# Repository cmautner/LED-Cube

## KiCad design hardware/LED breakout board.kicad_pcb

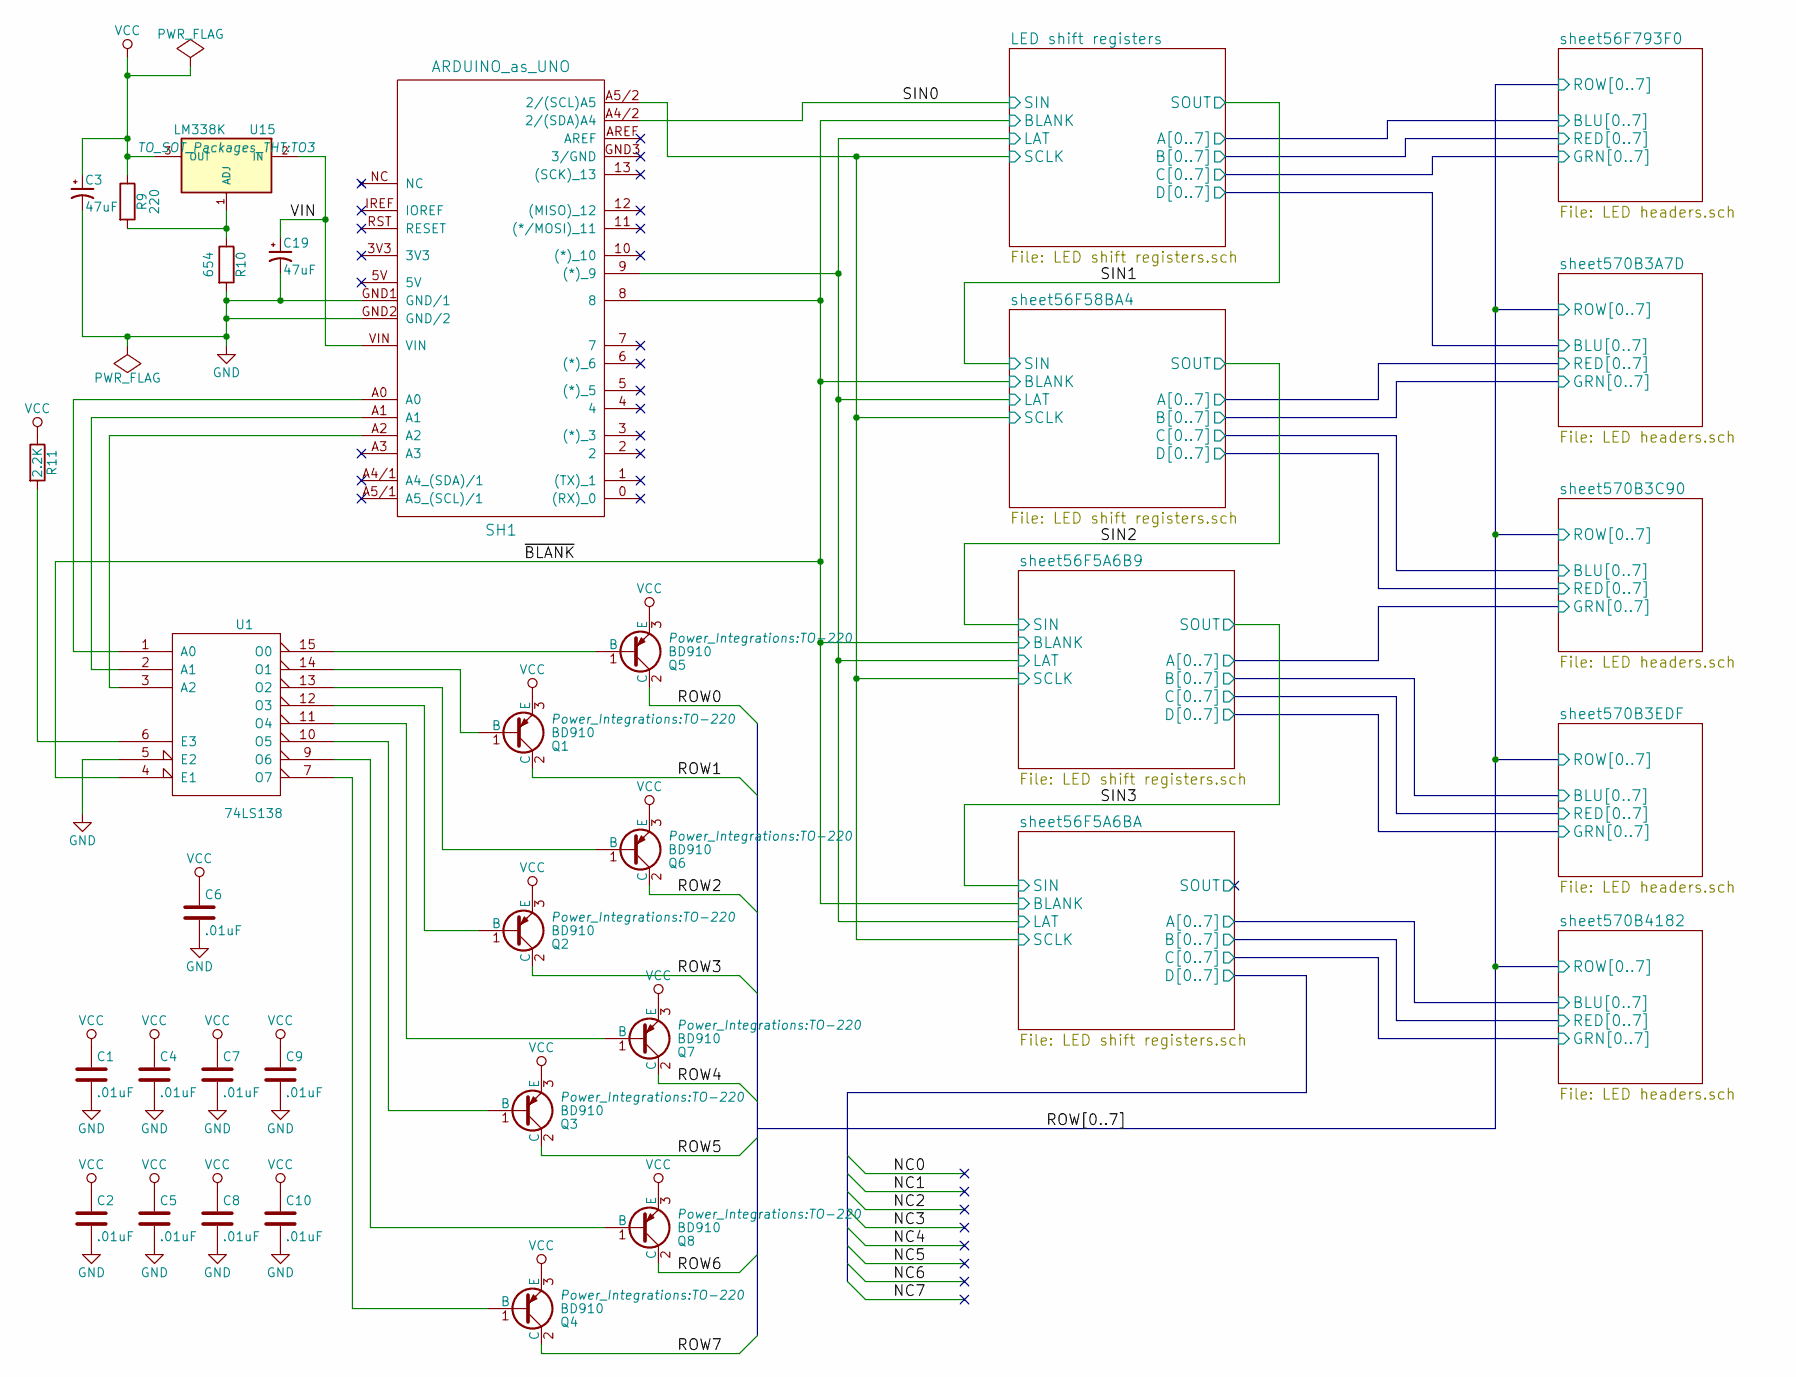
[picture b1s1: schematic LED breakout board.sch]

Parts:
C1, C2, C4, C5, C6, C7, C8, C9, C10: .01uF; C_Disc_D3_P2.5
C3, C19: 47uF; C_Rect_L7_W3.5_P5
Q1, Q2, Q3, Q4, Q5, Q6, Q7, Q8: BD910; TO-220
R9: 220; Resistor_Horizontal_RM10mm
R10: 654; Resistor_Horizontal_RM10mm
R11: 2.2K; Resistor_Horizontal_RM10mm
SH1: ARDUINO_as_UNO; ARDUINO_as_UNO_R3
U1: 74LS138; DIP-16_W7.62mm
U15: LM338K; TO3

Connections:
/LED shift registers/BLANK: SH1.8, U1.4 (E1); also elsewhere on the board
/LED shift registers/LAT: SH1.9 ((*)_9); also elsewhere on the board
/LED shift registers/SCLK: SH1.A5/2 (2/(SCL)A5); also elsewhere on the board
/LED shift registers/SIN: SH1.A4/2 (2/(SDA)A4); also elsewhere on the board
/ROW0: Q5.2 (C); also elsewhere on the board
/ROW1: Q1.2 (C); also elsewhere on the board
/ROW2: Q6.2 (C); also elsewhere on the board
/ROW3: Q2.2 (C); also elsewhere on the board
/ROW4: Q7.2 (C); also elsewhere on the board
/ROW5: Q3.2 (C); also elsewhere on the board
/ROW6: Q8.2 (C); also elsewhere on the board
/ROW7: Q4.2 (C); also elsewhere on the board
/VIN: C19.1, SH1.VIN, U15.2 (IN)
GND: C1.2, C2.2, C3.2, C4.2, C5.2, C6.2, C7.2, C8.2, C9.2, C10.2, C19.2, R10.2, SH1.GND1 (GND/1), SH1.GND2 (GND/2), U1.5 (E2), U1.8 (GND); also elsewhere on the board
unnamed: Q1.1 (B), U1.14 (O1)
unnamed: Q2.1 (B), U1.12 (O3)
unnamed: Q3.1 (B), U1.10 (O5)
unnamed: Q4.1 (B), U1.7 (O7)
unnamed: Q5.1 (B), U1.15 (O0)
unnamed: Q6.1 (B), U1.13 (O2)
unnamed: Q7.1 (B), U1.11 (O4)
unnamed: Q8.1 (B), U1.9 (O6)
unnamed: R9.2, R10.1, U15.1 (ADJ)
unnamed: R11.2, U1.6 (E3)
unnamed: SH1.A0, U1.1 (A0)
unnamed: SH1.A1, U1.2 (A1)
unnamed: SH1.A2, U1.3 (A2)
VCC: C1.1, C2.1, C3.1, C4.1, C5.1, C6.1, C7.1, C8.1, C9.1, C10.1, Q1.3 (E), Q2.3 (E), Q3.3 (E), Q4.3 (E), Q5.3 (E), Q6.3 (E), Q7.3 (E), Q8.3 (E), R9.1, R11.1, U1.16 (VCC), U15.3 (OUT); also elsewhere on the board

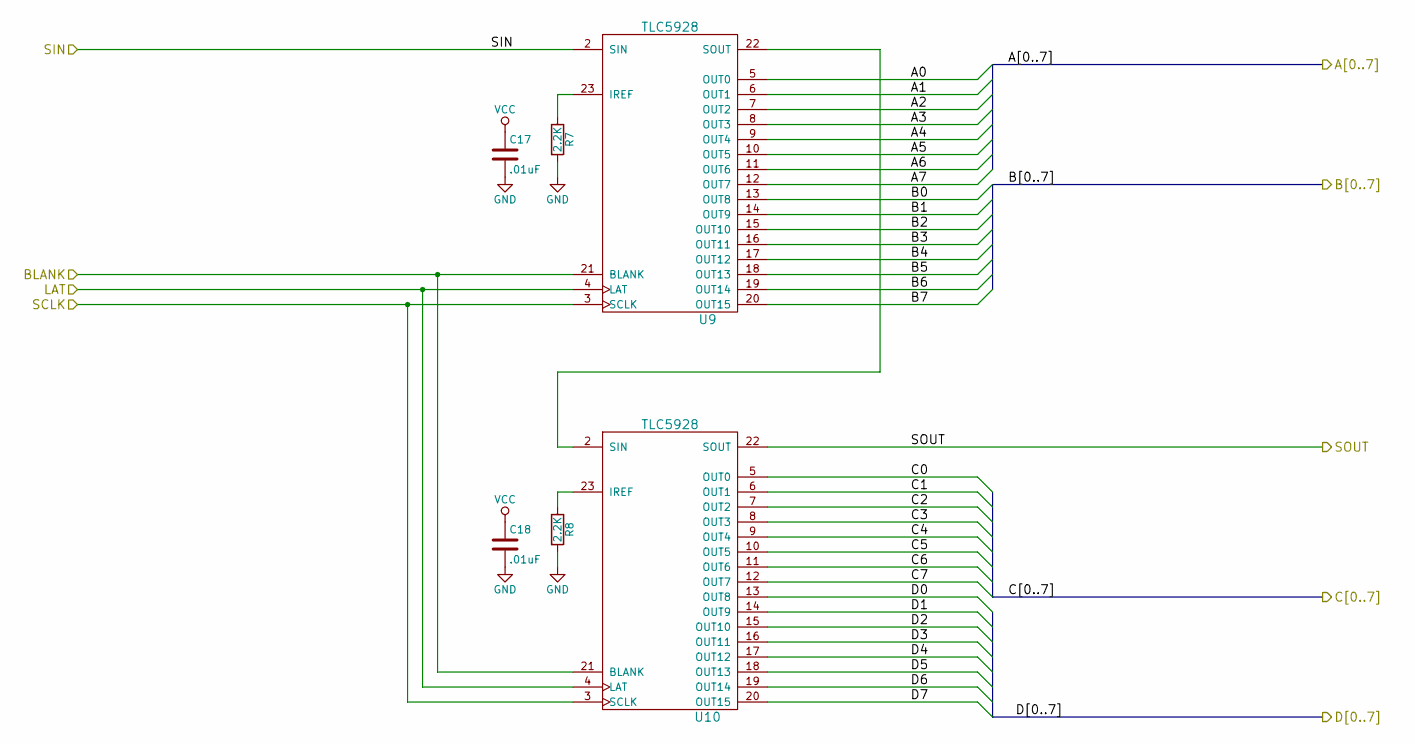
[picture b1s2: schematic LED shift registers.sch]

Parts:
C11, C12: .01uF; C_Disc_D3_P2.5
R1, R2: 2.2K; Resistor_Horizontal_RM10mm
U2, U3: TLC5928; DIP-24_W7.62mm

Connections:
/LED shift registers/A0: U2.5 (OUT0); also elsewhere on the board
/LED shift registers/A1: U2.6 (OUT1); also elsewhere on the board
/LED shift registers/A2: U2.7 (OUT2); also elsewhere on the board
/LED shift registers/A3: U2.8 (OUT3); also elsewhere on the board
/LED shift registers/A4: U2.9 (OUT4); also elsewhere on the board
/LED shift registers/A5: U2.10 (OUT5); also elsewhere on the board
/LED shift registers/A6: U2.11 (OUT6); also elsewhere on the board
/LED shift registers/A7: U2.12 (OUT7); also elsewhere on the board
/LED shift registers/B0: U2.13 (OUT8); also elsewhere on the board
/LED shift registers/B1: U2.14 (OUT9); also elsewhere on the board
/LED shift registers/B2: U2.15 (OUT10); also elsewhere on the board
/LED shift registers/B3: U2.16 (OUT11); also elsewhere on the board
/LED shift registers/B4: U2.17 (OUT12); also elsewhere on the board
/LED shift registers/B5: U2.18 (OUT13); also elsewhere on the board
/LED shift registers/B6: U2.19 (OUT14); also elsewhere on the board
/LED shift registers/B7: U2.20 (OUT15); also elsewhere on the board
/LED shift registers/BLANK: U2.21 (BLANK), U3.21 (BLANK); also elsewhere on the board
/LED shift registers/C0: U3.5 (OUT0); also elsewhere on the board
/LED shift registers/C1: U3.6 (OUT1); also elsewhere on the board
/LED shift registers/C2: U3.7 (OUT2); also elsewhere on the board
/LED shift registers/C3: U3.8 (OUT3); also elsewhere on the board
/LED shift registers/C4: U3.9 (OUT4); also elsewhere on the board
/LED shift registers/C5: U3.10 (OUT5); also elsewhere on the board
/LED shift registers/C6: U3.11 (OUT6); also elsewhere on the board
/LED shift registers/C7: U3.12 (OUT7); also elsewhere on the board
/LED shift registers/LAT: U2.4 (LAT), U3.4 (LAT); also elsewhere on the board
/LED shift registers/SCLK: U2.3 (SCLK), U3.3 (SCLK); also elsewhere on the board
/LED shift registers/SIN: U2.2 (SIN); also elsewhere on the board
/sheet56F58BA4/SIN: U3.22 (SOUT); also elsewhere on the board
/sheet570B3A7D/BLU0: U3.13 (OUT8); also elsewhere on the board
/sheet570B3A7D/BLU1: U3.14 (OUT9); also elsewhere on the board
/sheet570B3A7D/BLU2: U3.15 (OUT10); also elsewhere on the board
/sheet570B3A7D/BLU3: U3.16 (OUT11); also elsewhere on the board
/sheet570B3A7D/BLU4: U3.17 (OUT12); also elsewhere on the board
/sheet570B3A7D/BLU5: U3.18 (OUT13); also elsewhere on the board
/sheet570B3A7D/BLU6: U3.19 (OUT14); also elsewhere on the board
/sheet570B3A7D/BLU7: U3.20 (OUT15); also elsewhere on the board
GND: C11.2, C12.2, R1.2, R2.2, U2.1 (GND), U3.1 (GND); also elsewhere on the board
unnamed: R1.1, U2.23 (IREF)
unnamed: R2.1, U3.23 (IREF)
unnamed: U2.22 (SOUT), U3.2 (SIN)
VCC: C11.1, C12.1, U2.24 (VCC), U3.24 (VCC); also elsewhere on the board

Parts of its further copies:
C13, C14, C15, C16, C17, C18: .01uF; C_Disc_D3_P2.5
R3, R4, R5, R6, R7, R8: 2.2K; Resistor_Horizontal_RM10mm
U4, U5, U6, U7, U9, U10: TLC5928; DIP-24_W7.62mm

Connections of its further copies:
/LED shift registers/BLANK: U4.21 (BLANK), U5.21 (BLANK), U6.21 (BLANK), U7.21 (BLANK), U9.21 (BLANK), U10.21 (BLANK); also elsewhere on the board
/LED shift registers/LAT: U4.4 (LAT), U5.4 (LAT), U6.4 (LAT), U7.4 (LAT), U9.4 (LAT), U10.4 (LAT); also elsewhere on the board
/LED shift registers/SCLK: U4.3 (SCLK), U5.3 (SCLK), U6.3 (SCLK), U7.3 (SCLK), U9.3 (SCLK), U10.3 (SCLK); also elsewhere on the board
/sheet56F5A6B9/A0: U4.5 (OUT0); also elsewhere on the board
/sheet56F5A6B9/A1: U4.6 (OUT1); also elsewhere on the board
/sheet56F5A6B9/A2: U4.7 (OUT2); also elsewhere on the board
/sheet56F5A6B9/A3: U4.8 (OUT3); also elsewhere on the board
/sheet56F5A6B9/A4: U4.9 (OUT4); also elsewhere on the board
/sheet56F5A6B9/A5: U4.10 (OUT5); also elsewhere on the board
/sheet56F5A6B9/A6: U4.11 (OUT6); also elsewhere on the board
/sheet56F5A6B9/A7: U4.12 (OUT7); also elsewhere on the board
/sheet56F5A6B9/B0: U4.13 (OUT8); also elsewhere on the board
/sheet56F5A6B9/B1: U4.14 (OUT9); also elsewhere on the board
/sheet56F5A6B9/B2: U4.15 (OUT10); also elsewhere on the board
/sheet56F5A6B9/B3: U4.16 (OUT11); also elsewhere on the board
/sheet56F5A6B9/B4: U4.17 (OUT12); also elsewhere on the board
/sheet56F5A6B9/B5: U4.18 (OUT13); also elsewhere on the board
/sheet56F5A6B9/B6: U4.19 (OUT14); also elsewhere on the board
/sheet56F5A6B9/B7: U4.20 (OUT15); also elsewhere on the board
/sheet56F5A6B9/C0: U5.5 (OUT0); also elsewhere on the board
/sheet56F5A6B9/C1: U5.6 (OUT1); also elsewhere on the board
/sheet56F5A6B9/C2: U5.7 (OUT2); also elsewhere on the board
/sheet56F5A6B9/C3: U5.8 (OUT3); also elsewhere on the board
/sheet56F5A6B9/C4: U5.9 (OUT4); also elsewhere on the board
/sheet56F5A6B9/C5: U5.10 (OUT5); also elsewhere on the board
/sheet56F5A6B9/C6: U5.11 (OUT6); also elsewhere on the board
/sheet56F5A6B9/C7: U5.12 (OUT7); also elsewhere on the board
/sheet56F5A6B9/D0: U5.13 (OUT8); also elsewhere on the board
/sheet56F5A6B9/D1: U5.14 (OUT9); also elsewhere on the board
/sheet56F5A6B9/D2: U5.15 (OUT10); also elsewhere on the board
/sheet56F5A6B9/D3: U5.16 (OUT11); also elsewhere on the board
/sheet56F5A6B9/D4: U5.17 (OUT12); also elsewhere on the board
/sheet56F5A6B9/D5: U5.18 (OUT13); also elsewhere on the board
/sheet56F5A6B9/D6: U5.19 (OUT14); also elsewhere on the board
/sheet56F5A6B9/D7: U5.20 (OUT15); also elsewhere on the board
/sheet56F5A6B9/SIN: U4.2 (SIN), U10.22 (SOUT)
/sheet56F5A6BA/A0: U6.5 (OUT0); also elsewhere on the board
/sheet56F5A6BA/A1: U6.6 (OUT1); also elsewhere on the board
/sheet56F5A6BA/A2: U6.7 (OUT2); also elsewhere on the board
/sheet56F5A6BA/A3: U6.8 (OUT3); also elsewhere on the board
/sheet56F5A6BA/A4: U6.9 (OUT4); also elsewhere on the board
/sheet56F5A6BA/A5: U6.10 (OUT5); also elsewhere on the board
/sheet56F5A6BA/A6: U6.11 (OUT6); also elsewhere on the board
/sheet56F5A6BA/A7: U6.12 (OUT7); also elsewhere on the board
/sheet56F5A6BA/B0: U6.13 (OUT8); also elsewhere on the board
/sheet56F5A6BA/B1: U6.14 (OUT9); also elsewhere on the board
/sheet56F5A6BA/B2: U6.15 (OUT10); also elsewhere on the board
/sheet56F5A6BA/B3: U6.16 (OUT11); also elsewhere on the board
/sheet56F5A6BA/B4: U6.17 (OUT12); also elsewhere on the board
/sheet56F5A6BA/B5: U6.18 (OUT13); also elsewhere on the board
/sheet56F5A6BA/B6: U6.19 (OUT14); also elsewhere on the board
/sheet56F5A6BA/B7: U6.20 (OUT15); also elsewhere on the board
/sheet56F5A6BA/C0: U7.5 (OUT0); also elsewhere on the board
/sheet56F5A6BA/C1: U7.6 (OUT1); also elsewhere on the board
/sheet56F5A6BA/C2: U7.7 (OUT2); also elsewhere on the board
/sheet56F5A6BA/C3: U7.8 (OUT3); also elsewhere on the board
/sheet56F5A6BA/C4: U7.9 (OUT4); also elsewhere on the board
/sheet56F5A6BA/C5: U7.10 (OUT5); also elsewhere on the board
/sheet56F5A6BA/C6: U7.11 (OUT6); also elsewhere on the board
/sheet56F5A6BA/C7: U7.12 (OUT7); also elsewhere on the board
/sheet56F5A6BA/SIN: U5.22 (SOUT), U6.2 (SIN)
/sheet56F58BA4/A0: U9.5 (OUT0); also elsewhere on the board
/sheet56F58BA4/A1: U9.6 (OUT1); also elsewhere on the board
/sheet56F58BA4/A2: U9.7 (OUT2); also elsewhere on the board
/sheet56F58BA4/A3: U9.8 (OUT3); also elsewhere on the board
/sheet56F58BA4/A4: U9.9 (OUT4); also elsewhere on the board
/sheet56F58BA4/A5: U9.10 (OUT5); also elsewhere on the board
/sheet56F58BA4/A6: U9.11 (OUT6); also elsewhere on the board
/sheet56F58BA4/A7: U9.12 (OUT7); also elsewhere on the board
/sheet56F58BA4/B0: U9.13 (OUT8); also elsewhere on the board
/sheet56F58BA4/B1: U9.14 (OUT9); also elsewhere on the board
/sheet56F58BA4/B2: U9.15 (OUT10); also elsewhere on the board
/sheet56F58BA4/B3: U9.16 (OUT11); also elsewhere on the board
/sheet56F58BA4/B4: U9.17 (OUT12); also elsewhere on the board
/sheet56F58BA4/B5: U9.18 (OUT13); also elsewhere on the board
/sheet56F58BA4/B6: U9.19 (OUT14); also elsewhere on the board
/sheet56F58BA4/B7: U9.20 (OUT15); also elsewhere on the board
/sheet56F58BA4/D0: U10.13 (OUT8); also elsewhere on the board
/sheet56F58BA4/D1: U10.14 (OUT9); also elsewhere on the board
/sheet56F58BA4/D2: U10.15 (OUT10); also elsewhere on the board
/sheet56F58BA4/D3: U10.16 (OUT11); also elsewhere on the board
/sheet56F58BA4/D4: U10.17 (OUT12); also elsewhere on the board
/sheet56F58BA4/D5: U10.18 (OUT13); also elsewhere on the board
/sheet56F58BA4/D6: U10.19 (OUT14); also elsewhere on the board
/sheet56F58BA4/D7: U10.20 (OUT15); also elsewhere on the board
/sheet56F58BA4/SIN: U9.2 (SIN); also elsewhere on the board
/sheet570B3C90/BLU0: U10.5 (OUT0); also elsewhere on the board
/sheet570B3C90/BLU1: U10.6 (OUT1); also elsewhere on the board
/sheet570B3C90/BLU2: U10.7 (OUT2); also elsewhere on the board
/sheet570B3C90/BLU3: U10.8 (OUT3); also elsewhere on the board
/sheet570B3C90/BLU4: U10.9 (OUT4); also elsewhere on the board
/sheet570B3C90/BLU5: U10.10 (OUT5); also elsewhere on the board
/sheet570B3C90/BLU6: U10.11 (OUT6); also elsewhere on the board
/sheet570B3C90/BLU7: U10.12 (OUT7); also elsewhere on the board
GND: C13.2, C14.2, C15.2, C16.2, C17.2, C18.2, R3.2, R4.2, R5.2, R6.2, R7.2, R8.2, U4.1 (GND), U5.1 (GND), U6.1 (GND), U7.1 (GND), U9.1 (GND), U10.1 (GND); also elsewhere on the board
unnamed: R3.1, U4.23 (IREF)
unnamed: R4.1, U5.23 (IREF)
unnamed: R5.1, U6.23 (IREF)
unnamed: R6.1, U7.23 (IREF)
unnamed: R7.1, U9.23 (IREF)
unnamed: R8.1, U10.23 (IREF)
unnamed: U4.22 (SOUT), U5.2 (SIN)
unnamed: U6.22 (SOUT), U7.2 (SIN)
unnamed: U9.22 (SOUT), U10.2 (SIN)
VCC: C13.1, C14.1, C15.1, C16.1, C17.1, C18.1, U4.24 (VCC), U5.24 (VCC), U6.24 (VCC), U7.24 (VCC), U9.24 (VCC), U10.24 (VCC); also elsewhere on the board

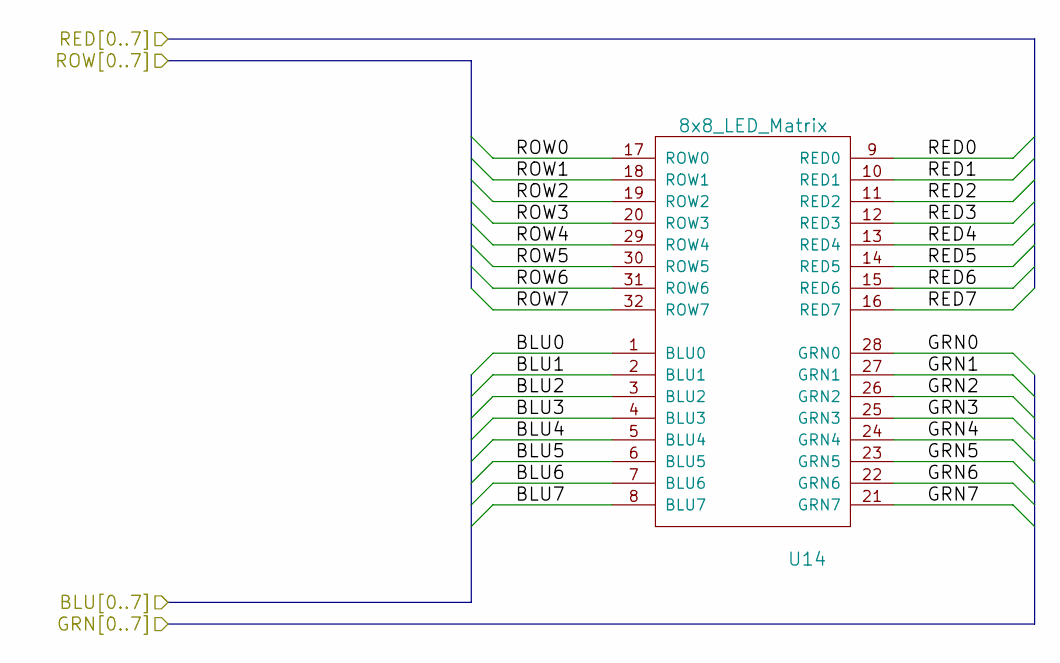
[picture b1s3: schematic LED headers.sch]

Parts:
U8: 8x8_LED_Matrix

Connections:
/LED shift registers/A0: U8.1 (BLU0); also elsewhere on the board
/LED shift registers/A1: U8.2 (BLU1); also elsewhere on the board
/LED shift registers/A2: U8.3 (BLU2); also elsewhere on the board
/LED shift registers/A3: U8.4 (BLU3); also elsewhere on the board
/LED shift registers/A4: U8.5 (BLU4); also elsewhere on the board
/LED shift registers/A5: U8.6 (BLU5); also elsewhere on the board
/LED shift registers/A6: U8.7 (BLU6); also elsewhere on the board
/LED shift registers/A7: U8.8 (BLU7); also elsewhere on the board
/LED shift registers/B0: U8.9 (RED0); also elsewhere on the board
/LED shift registers/B1: U8.10 (RED1); also elsewhere on the board
/LED shift registers/B2: U8.11 (RED2); also elsewhere on the board
/LED shift registers/B3: U8.12 (RED3); also elsewhere on the board
/LED shift registers/B4: U8.13 (RED4); also elsewhere on the board
/LED shift registers/B5: U8.14 (RED5); also elsewhere on the board
/LED shift registers/B6: U8.15 (RED6); also elsewhere on the board
/LED shift registers/B7: U8.16 (RED7); also elsewhere on the board
/LED shift registers/C0: U8.28 (GRN0); also elsewhere on the board
/LED shift registers/C1: U8.27 (GRN1); also elsewhere on the board
/LED shift registers/C2: U8.26 (GRN2); also elsewhere on the board
/LED shift registers/C3: U8.25 (GRN3); also elsewhere on the board
/LED shift registers/C4: U8.24 (GRN4); also elsewhere on the board
/LED shift registers/C5: U8.23 (GRN5); also elsewhere on the board
/LED shift registers/C6: U8.22 (GRN6); also elsewhere on the board
/LED shift registers/C7: U8.21 (GRN7); also elsewhere on the board
/ROW0: U8.17 (ROW0); also elsewhere on the board
/ROW1: U8.18 (ROW1); also elsewhere on the board
/ROW2: U8.19 (ROW2); also elsewhere on the board
/ROW3: U8.20 (ROW3); also elsewhere on the board
/ROW4: U8.29 (ROW4); also elsewhere on the board
/ROW5: U8.30 (ROW5); also elsewhere on the board
/ROW6: U8.31 (ROW6); also elsewhere on the board
/ROW7: U8.32 (ROW7); also elsewhere on the board

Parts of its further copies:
U11, U12, U13, U14: 8x8_LED_Matrix

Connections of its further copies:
/ROW0: U11.17 (ROW0), U12.17 (ROW0), U13.17 (ROW0), U14.17 (ROW0); also elsewhere on the board
/ROW1: U11.18 (ROW1), U12.18 (ROW1), U13.18 (ROW1), U14.18 (ROW1); also elsewhere on the board
/ROW2: U11.19 (ROW2), U12.19 (ROW2), U13.19 (ROW2), U14.19 (ROW2); also elsewhere on the board
/ROW3: U11.20 (ROW3), U12.20 (ROW3), U13.20 (ROW3), U14.20 (ROW3); also elsewhere on the board
/ROW4: U11.29 (ROW4), U12.29 (ROW4), U13.29 (ROW4), U14.29 (ROW4); also elsewhere on the board
/ROW5: U11.30 (ROW5), U12.30 (ROW5), U13.30 (ROW5), U14.30 (ROW5); also elsewhere on the board
/ROW6: U11.31 (ROW6), U12.31 (ROW6), U13.31 (ROW6), U14.31 (ROW6); also elsewhere on the board
/ROW7: U11.32 (ROW7), U12.32 (ROW7), U13.32 (ROW7), U14.32 (ROW7); also elsewhere on the board
/sheet56F5A6B9/A0: U12.28 (GRN0); also elsewhere on the board
/sheet56F5A6B9/A1: U12.27 (GRN1); also elsewhere on the board
/sheet56F5A6B9/A2: U12.26 (GRN2); also elsewhere on the board
/sheet56F5A6B9/A3: U12.25 (GRN3); also elsewhere on the board
/sheet56F5A6B9/A4: U12.24 (GRN4); also elsewhere on the board
/sheet56F5A6B9/A5: U12.23 (GRN5); also elsewhere on the board
/sheet56F5A6B9/A6: U12.22 (GRN6); also elsewhere on the board
/sheet56F5A6B9/A7: U12.21 (GRN7); also elsewhere on the board
/sheet56F5A6B9/B0: U13.1 (BLU0); also elsewhere on the board
/sheet56F5A6B9/B1: U13.2 (BLU1); also elsewhere on the board
/sheet56F5A6B9/B2: U13.3 (BLU2); also elsewhere on the board
/sheet56F5A6B9/B3: U13.4 (BLU3); also elsewhere on the board
/sheet56F5A6B9/B4: U13.5 (BLU4); also elsewhere on the board
/sheet56F5A6B9/B5: U13.6 (BLU5); also elsewhere on the board
/sheet56F5A6B9/B6: U13.7 (BLU6); also elsewhere on the board
/sheet56F5A6B9/B7: U13.8 (BLU7); also elsewhere on the board
/sheet56F5A6B9/C0: U13.9 (RED0); also elsewhere on the board
/sheet56F5A6B9/C1: U13.10 (RED1); also elsewhere on the board
/sheet56F5A6B9/C2: U13.11 (RED2); also elsewhere on the board
/sheet56F5A6B9/C3: U13.12 (RED3); also elsewhere on the board
/sheet56F5A6B9/C4: U13.13 (RED4); also elsewhere on the board
/sheet56F5A6B9/C5: U13.14 (RED5); also elsewhere on the board
/sheet56F5A6B9/C6: U13.15 (RED6); also elsewhere on the board
/sheet56F5A6B9/C7: U13.16 (RED7); also elsewhere on the board
/sheet56F5A6B9/D0: U13.28 (GRN0); also elsewhere on the board
/sheet56F5A6B9/D1: U13.27 (GRN1); also elsewhere on the board
/sheet56F5A6B9/D2: U13.26 (GRN2); also elsewhere on the board
/sheet56F5A6B9/D3: U13.25 (GRN3); also elsewhere on the board
/sheet56F5A6B9/D4: U13.24 (GRN4); also elsewhere on the board
/sheet56F5A6B9/D5: U13.23 (GRN5); also elsewhere on the board
/sheet56F5A6B9/D6: U13.22 (GRN6); also elsewhere on the board
/sheet56F5A6B9/D7: U13.21 (GRN7); also elsewhere on the board
/sheet56F5A6BA/A0: U14.1 (BLU0); also elsewhere on the board
/sheet56F5A6BA/A1: U14.2 (BLU1); also elsewhere on the board
/sheet56F5A6BA/A2: U14.3 (BLU2); also elsewhere on the board
/sheet56F5A6BA/A3: U14.4 (BLU3); also elsewhere on the board
/sheet56F5A6BA/A4: U14.5 (BLU4); also elsewhere on the board
/sheet56F5A6BA/A5: U14.6 (BLU5); also elsewhere on the board
/sheet56F5A6BA/A6: U14.7 (BLU6); also elsewhere on the board
/sheet56F5A6BA/A7: U14.8 (BLU7); also elsewhere on the board
/sheet56F5A6BA/B0: U14.9 (RED0); also elsewhere on the board
/sheet56F5A6BA/B1: U14.10 (RED1); also elsewhere on the board
/sheet56F5A6BA/B2: U14.11 (RED2); also elsewhere on the board
/sheet56F5A6BA/B3: U14.12 (RED3); also elsewhere on the board
/sheet56F5A6BA/B4: U14.13 (RED4); also elsewhere on the board
/sheet56F5A6BA/B5: U14.14 (RED5); also elsewhere on the board
/sheet56F5A6BA/B6: U14.15 (RED6); also elsewhere on the board
/sheet56F5A6BA/B7: U14.16 (RED7); also elsewhere on the board
/sheet56F5A6BA/C0: U14.28 (GRN0); also elsewhere on the board
/sheet56F5A6BA/C1: U14.27 (GRN1); also elsewhere on the board
/sheet56F5A6BA/C2: U14.26 (GRN2); also elsewhere on the board
/sheet56F5A6BA/C3: U14.25 (GRN3); also elsewhere on the board
/sheet56F5A6BA/C4: U14.24 (GRN4); also elsewhere on the board
/sheet56F5A6BA/C5: U14.23 (GRN5); also elsewhere on the board
/sheet56F5A6BA/C6: U14.22 (GRN6); also elsewhere on the board
/sheet56F5A6BA/C7: U14.21 (GRN7); also elsewhere on the board
/sheet56F58BA4/A0: U11.9 (RED0); also elsewhere on the board
/sheet56F58BA4/A1: U11.10 (RED1); also elsewhere on the board
/sheet56F58BA4/A2: U11.11 (RED2); also elsewhere on the board
/sheet56F58BA4/A3: U11.12 (RED3); also elsewhere on the board
/sheet56F58BA4/A4: U11.13 (RED4); also elsewhere on the board
/sheet56F58BA4/A5: U11.14 (RED5); also elsewhere on the board
/sheet56F58BA4/A6: U11.15 (RED6); also elsewhere on the board
/sheet56F58BA4/A7: U11.16 (RED7); also elsewhere on the board
/sheet56F58BA4/B0: U11.28 (GRN0); also elsewhere on the board
/sheet56F58BA4/B1: U11.27 (GRN1); also elsewhere on the board
/sheet56F58BA4/B2: U11.26 (GRN2); also elsewhere on the board
/sheet56F58BA4/B3: U11.25 (GRN3); also elsewhere on the board
/sheet56F58BA4/B4: U11.24 (GRN4); also elsewhere on the board
/sheet56F58BA4/B5: U11.23 (GRN5); also elsewhere on the board
/sheet56F58BA4/B6: U11.22 (GRN6); also elsewhere on the board
/sheet56F58BA4/B7: U11.21 (GRN7); also elsewhere on the board
/sheet56F58BA4/D0: U12.9 (RED0); also elsewhere on the board
/sheet56F58BA4/D1: U12.10 (RED1); also elsewhere on the board
/sheet56F58BA4/D2: U12.11 (RED2); also elsewhere on the board
/sheet56F58BA4/D3: U12.12 (RED3); also elsewhere on the board
/sheet56F58BA4/D4: U12.13 (RED4); also elsewhere on the board
/sheet56F58BA4/D5: U12.14 (RED5); also elsewhere on the board
/sheet56F58BA4/D6: U12.15 (RED6); also elsewhere on the board
/sheet56F58BA4/D7: U12.16 (RED7); also elsewhere on the board
/sheet570B3A7D/BLU0: U11.1 (BLU0); also elsewhere on the board
/sheet570B3A7D/BLU1: U11.2 (BLU1); also elsewhere on the board
/sheet570B3A7D/BLU2: U11.3 (BLU2); also elsewhere on the board
/sheet570B3A7D/BLU3: U11.4 (BLU3); also elsewhere on the board
/sheet570B3A7D/BLU4: U11.5 (BLU4); also elsewhere on the board
/sheet570B3A7D/BLU5: U11.6 (BLU5); also elsewhere on the board
/sheet570B3A7D/BLU6: U11.7 (BLU6); also elsewhere on the board
/sheet570B3A7D/BLU7: U11.8 (BLU7); also elsewhere on the board
/sheet570B3C90/BLU0: U12.1 (BLU0); also elsewhere on the board
/sheet570B3C90/BLU1: U12.2 (BLU1); also elsewhere on the board
/sheet570B3C90/BLU2: U12.3 (BLU2); also elsewhere on the board
/sheet570B3C90/BLU3: U12.4 (BLU3); also elsewhere on the board
/sheet570B3C90/BLU4: U12.5 (BLU4); also elsewhere on the board
/sheet570B3C90/BLU5: U12.6 (BLU5); also elsewhere on the board
/sheet570B3C90/BLU6: U12.7 (BLU6); also elsewhere on the board
/sheet570B3C90/BLU7: U12.8 (BLU7); also elsewhere on the board

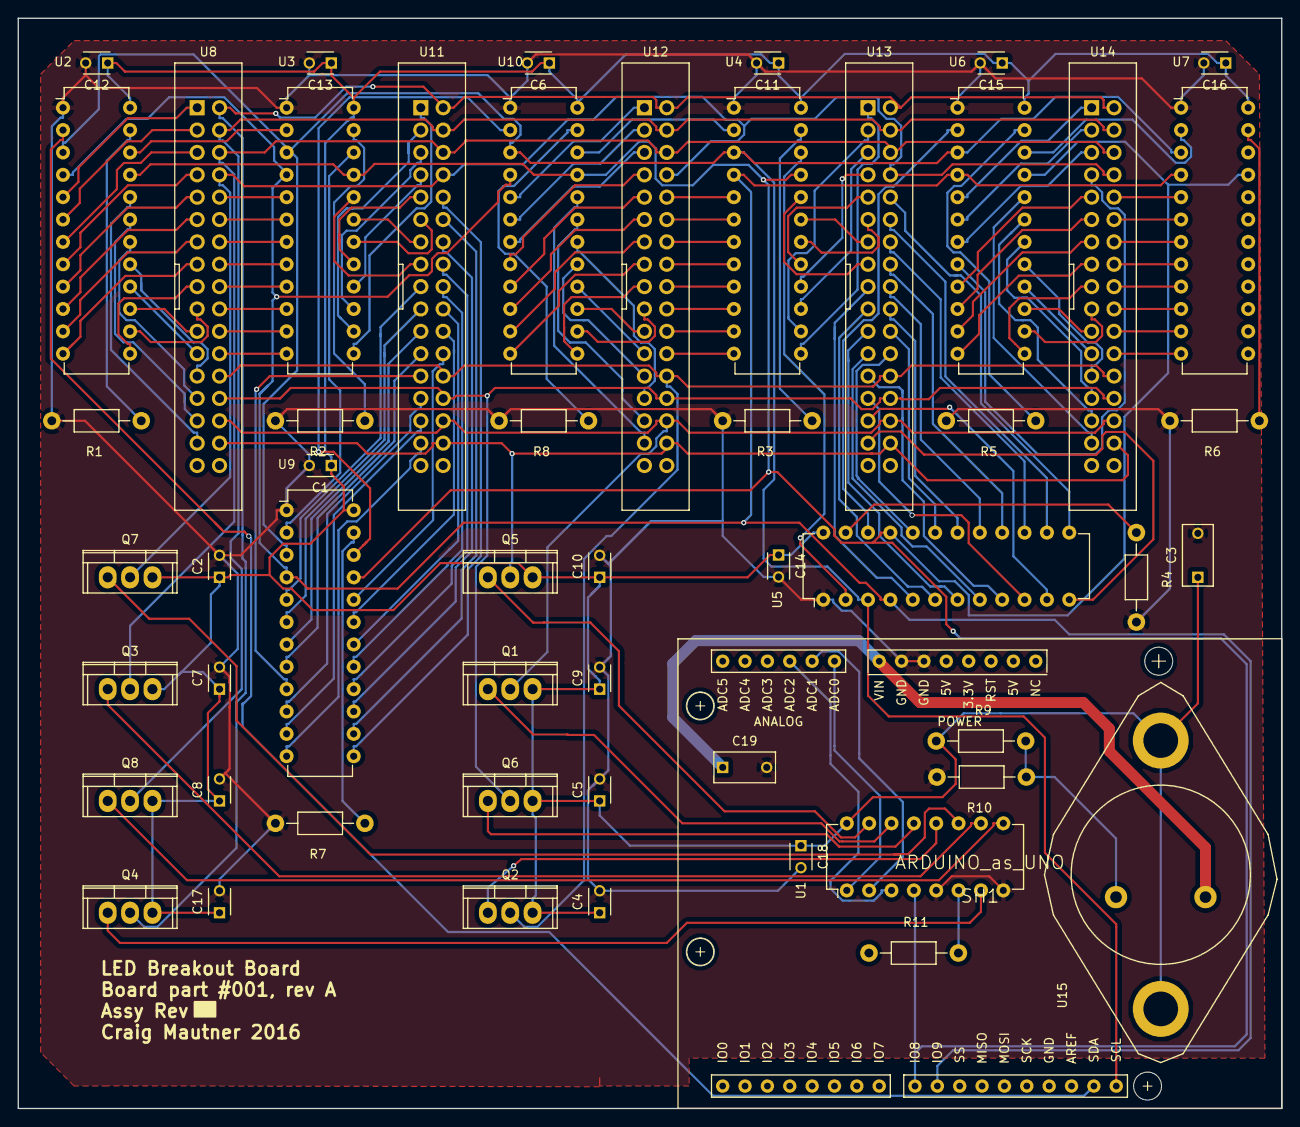
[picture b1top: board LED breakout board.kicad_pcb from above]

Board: 2 copper layers, 143.5 x 123.8 mm, 54 parts (0 on the bottom side), 163 nets.

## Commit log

2016-05-03 :confetti_ball: Added .gitattributes & .gitignore files
2016-05-03 Adding first files
    I believe these are the basic files needed to create and program the
    board. I will add the docs next
2016-05-10 Speed up refresh
    The data line is now changed when the clock line falls. That saves one
    cycle but means that the clock line must be high when CLOCK_DATA() is
    called.
    The BLANK_ signal is now LOW all the time.
    The LED pattern is a little more interesting. Red brightens, Green
    fades, blue brightens.
2016-05-11 Save something that kinda works
    But not as well as the last checkin
2016-06-19 Rows and LEDs updating correctly
    At last!
2016-06-20 Not working but want to save this before I revert
2016-06-20 Revert "Not working but want to save this before I revert"
    This reverts commit ac0a81957a16fac9b56a452baf793fa43df07653.
2016-06-20 Two bit intensity
2016-06-20 Renamed TimerInterrupt to Refresh
2016-06-21 First animation is working
2016-06-21 sped up animation and doubled the line width to emphasize the moving band
2016-06-25 Added user input, cleaned up loop timing, new pattern
    Added the ability to read IO7 pin to allow the pattern to change.
    Changed the timing to be able to be used for larger cycles than 6.
    Added a modified waterfall pattern that gradually changes the color.
2016-06-28 Switch to DiscodelicLib library
    Move common code into Arduino library.
2016-07-06 Adding a new program to generate all color patterns
2016-07-06 Renamed Patterns to Palette
2016-07-06 Slowed down refresh and removed panel dump.
2016-07-10 Remove predictability
    Color changes were in sync with panel changes so the patterns
    weren't changing as often as they were intended.
    Also cleaned up the timing to let the interrupt drive the animation
    rather than dividing down the interrupt.
2016-08-11 First text example
2017-03-07 Got Hello World printing on all 5 panels. Either scrolling or static. Working with the latest Discodelic library.
2017-03-11 Fixed all of the wide panel problems. Renamed LED_board app to Waterfall.
2017-03-13 Eliminate flash. This also required reconnecting the BLANK_ line to the 74LS138 in hardware which had been disconnected previously.
2017-03-15 Converted over to new library form where the library takes care of the interrupt timer and turning off and on the LEDs while rendering.
2017-03-18 First cut at a snake game. Self playing. Next cut to be greedy as it aims for food.
2017-03-21 Fixed all bugs related to moving in bad direction. Set up auto play. Fixed colors.
2017-03-21 Random was resetting the seed to the same few combinations every time. Adding in micros() after each death makes it more random. The real solution is to extract the reset from setup().
2017-03-21 No logic changes, just rearranged code and added comments.
2017-04-08 Fireworks!
2017-04-08 Added debug which tracked down the problem with fireworks that start on the top and span a corner end up on two sides of the top. Fixed by starting all fireworks on the sides.
